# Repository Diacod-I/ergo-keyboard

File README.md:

# My Ergonomic Keyboard

I have a ton of cramps and metacarpal pain due to typing on small keyboards like the Macbook keyboard (small relative to my larger-than-average hands). I'm going to solve that with an ergonomic keyboard. <br/>

Some guidelines for what I want:
- Keep it simple and go with QWERTY.
- Linear over staggered, but I need to aptly position the column based on my hand measurements.
- Split, so that I can position my arms more freely on a table.

I'm going to add all my work related to this here.

## Build Log
### 2/8/2026 (Newest update!)

#### Did today
1) Manually measured my hands to understand and evaluate an ideal finger placement (since I didn't have a touch screen to test with).
<div align="center">

<p>Figure 1. Manual calculations</p><br/>
</div>

2) Filled the MCU pin map: matrix on P2–P10 (cols P2–P6, rows P7–P10), split data on P1, VCC/GND on the rails. Same pads on both halves (identical firmware; QMK handles the split). Left P0 + P14 -> P21 free for the OLED SPI bus / shift-registers later.

3) Started assigning nets directly on the controller pads in KiCad.

4) Wired the split link: typed a new data net onto each controller's P1 and each TRRS jack, plus VCC/GND. Both jacks assigned identically so the cable ties the halves together correctly.
Set up git for the project + .gitignore.
<div align="center">

<p>Figure 2. Ergogen Key Layout</p><br/>
</div>

<div align="center">

<p>Figure 3. KiCAD PCB layout before net assignment</p><br/>
</div>

#### Learned

- Blue ratsnest lines = connections that exist but aren't copper yet. Routing = turning every blue line into a trace. When they're all gone, it's routed.
- A net only exists once a pad uses it. I had to type data into existence (it wasn't in the dropdown).
- TRRS: exact pad doesn't matter, but data/VCC/GND must be on matching contacts on both jacks or the split won't talk. Sleeve = GND by convention.
Important: board.kicad_pcb now has hand edits (outline curves + net assignments) that are NOT in config.yaml.

#### Still open

- Finish assigning all controller pads -> route the matrix -> ground pour -> DRC -> Gerbers -> order.
- Keymap dry-run (flash the Corne keymap.c, settle hold-vs-toggle) - **not started**.
- OLED v2: scaffolded + commented out, parked until a test rig.

### 13/3/2026
- Nevermind, we stick to QWERTY

### 12/3/2026
- I'm considering the layout amongst DVORAK and Coleman-DH from [the Knucklehead layout](https://github.com/minusfive/knucklehead/blob/main/README.md)

### 11/3/2026
- Making the plan for what I wanna make in my keyboard. Following is some ideas that I am considering
    1) Corne style split keyboard (easy to carry around) 
    2) Ortholinear columns with a slightly wider gap between each other for my big hands.
    3) VIM focused key layout 
    4) LED backlight 
    5) Arm rest????
    6) Check out bluetooth connection across the split keyboard along with the cable option just in case.
- I am considering Ergogen but there should be other ways to make the design.
- Roadmap would something like the following:
    1) Design PCB and key layout
    2) Make the PCB connections
    3) Buy the microcontrollers and extra parts
    4) Get the PCB made
    5) Get Soldering kit and solder everything
    6) Fix everything together
    7) Code the microcontroller logic and key mapping logic

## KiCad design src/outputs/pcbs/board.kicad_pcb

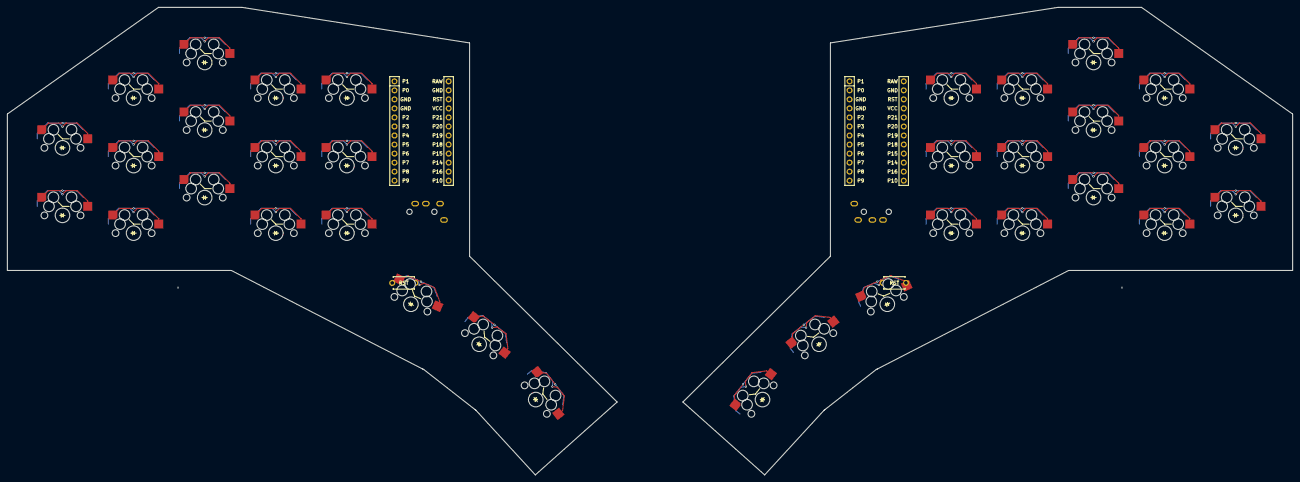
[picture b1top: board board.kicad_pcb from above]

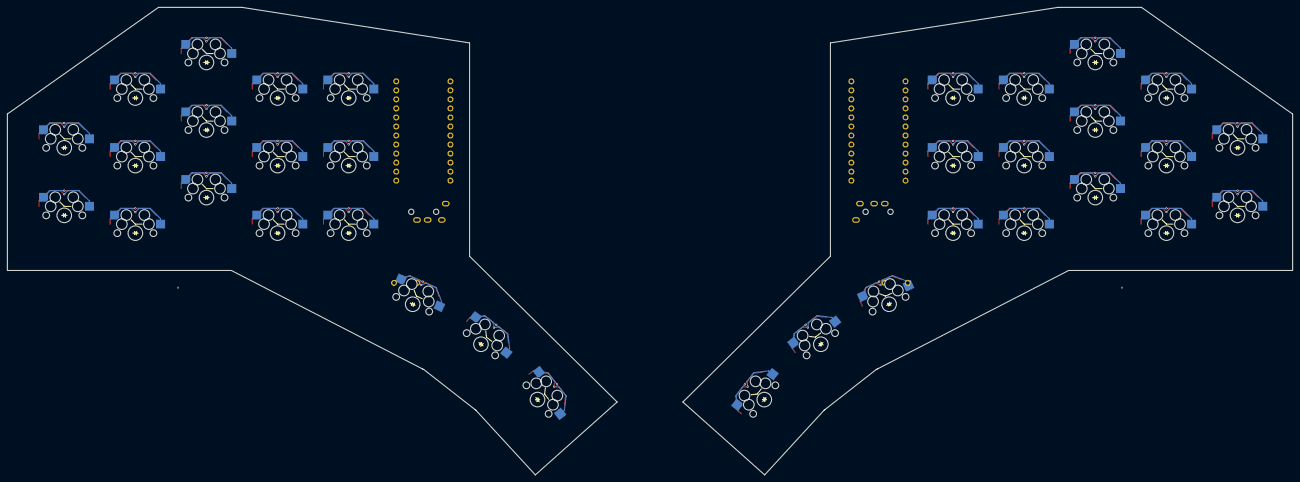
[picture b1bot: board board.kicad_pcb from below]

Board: 2 copper layers, 361.5 x 131.5 mm, 74 parts (34 on the bottom side), 60 nets.

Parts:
D1, D2, D3, D4, D5, D6, D7, D8, D9, D10, D11, D12, D13, D14, D15, D16, D17, D18, D19, D20, D21, D22, D23, D24, D25, D26, D27, D28, D29, D30, D31, D32, D33, D34: diode_tht_sod123
MCU1, MCU2: mcu_nice_nano
RST1, RST2: reset_switch_tht_top
S1, S2, S3, S4, S5, S6, S7, S8, S9, S10, S11, S12, S13, S14, S15, S16, S17, S18, S19, S20, S21, S22, S23, S24, S25, S26, S27, S28, S29, S30, S31, S32, S33, S34: switch_mx
TRRS1, TRRS2: trrs_pj320a

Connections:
GND: MCU1.2, MCU1.21, MCU1.22, MCU2.2, MCU2.21, MCU2.22, RST1.2, RST2.2
P0: MCU1.23, MCU2.23
P2: MCU1.20, MCU2.20
P14: MCU1.10, MCU2.10
P15: MCU1.9, MCU2.9
P16: MCU1.11, MCU2.11
P18: MCU1.8, MCU2.8
P19: MCU1.7, MCU2.7
P20: MCU1.6, MCU2.6
P21: MCU1.5, MCU2.5
R1: TRRS1.5, TRRS2.5
R2: TRRS1.3, TRRS2.3
RAW: MCU1.1, MCU2.1
RST: MCU1.3, MCU2.3, RST1.1, RST2.1
SL: TRRS1.2, TRRS2.2
TP: TRRS1.4, TRRS2.4
VCC: MCU1.4, MCU2.4
col0: S1.1, S2.1, S18.1, S19.1
col1: MCU2.19, S3.1, S4.1, S5.1, S20.1, S21.1, S22.1
col2: MCU2.18, S6.1, S7.1, S8.1, S17.1, S23.1, S24.1, S25.1, S34.1
col3: MCU2.17, S9.1, S10.1, S11.1, S16.1, S26.1, S27.1, S28.1, S33.1
col4: MCU2.16, S12.1, S13.1, S14.1, S15.1, S29.1, S30.1, S31.1, S32.1
matrix_index_bottom: D9.2, S9.2
matrix_index_home: D10.2, S10.2
matrix_index_top: D11.2, S11.2
matrix_inner_bottom: D12.2, S12.2
matrix_inner_home: D13.2, S13.2
matrix_inner_top: D14.2, S14.2
matrix_middle_bottom: D6.2, S6.2
matrix_middle_home: D7.2, S7.2
matrix_middle_top: D8.2, S8.2
matrix_pinky_home: D1.2, S1.2
matrix_pinky_top: D2.2, S2.2
matrix_ring_bottom: D3.2, S3.2
matrix_ring_home: D4.2, S4.2
matrix_ring_top: D5.2, S5.2
mirror_matrix_index_bottom: D26.2, S26.2
mirror_matrix_index_home: D27.2, S27.2
mirror_matrix_index_top: D28.2, S28.2
mirror_matrix_inner_bottom: D29.2, S29.2
mirror_matrix_inner_home: D30.2, S30.2
mirror_matrix_inner_top: D31.2, S31.2
mirror_matrix_middle_bottom: D23.2, S23.2
mirror_matrix_middle_home: D24.2, S24.2
mirror_matrix_middle_top: D25.2, S25.2
mirror_matrix_pinky_home: D18.2, S18.2
mirror_matrix_pinky_top: D19.2, S19.2
mirror_matrix_ring_bottom: D20.2, S20.2
mirror_matrix_ring_home: D21.2, S21.2
mirror_matrix_ring_top: D22.2, S22.2
mirror_thumbfan_t_far_thumb: D34.2, S34.2
mirror_thumbfan_t_mid_thumb: D33.2, S33.2
mirror_thumbfan_t_near_thumb: D32.2, S32.2
row0: D2.1, D5.1, D8.1, D11.1, D14.1, D19.1, D22.1, D25.1, D28.1, D31.1, MCU2.15
row1: D1.1, D4.1, D7.1, D10.1, D13.1, D18.1, D21.1, D24.1, D27.1, D30.1, MCU2.14
row2: D3.1, D6.1, D9.1, D12.1, D20.1, D23.1, D26.1, D29.1, MCU2.13
row3: D15.1, D16.1, D17.1, D32.1, D33.1, D34.1, MCU2.12
thumbfan_t_far_thumb: D17.2, S17.2
thumbfan_t_mid_thumb: D16.2, S16.2
thumbfan_t_near_thumb: D15.2, S15.2

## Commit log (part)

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2026-03-11 Genesis Commit
2026-03-12 New log - (12/3/2026)
